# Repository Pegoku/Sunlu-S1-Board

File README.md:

# Sunlu S1 Filament Dryer Controller

Drop-in replacement controller board for the Sunlu S1 filament dryer. Features an STM32C011F4P6 microcontroller, 1.8" ST7735 TFT display, dual NTC temperature sensing, and precise PWM heater control; all optimized to fit in just 16 KB of flash. 

## Table of Contents
- [Overview](#overview)
- [Features](#features)
- [Quick Start](#quick-start)
- [User Guide](#user-guide)
- [Hardware](#hardware)
- [Technical Specs](#technical-specs)
- [Development](#development)
- [License](#license)

## Overview

Complete replacement for the stock Sunlu S1 control board, maintaining compatibility with the original heating element, chamber, and power connections. Adds a color TFT display in landscape mode and two-button navigation for precise temperature and time control (30–70°C configurable range, exceeding the stock 35–55°C limit).

The firmware uses integer-only math, dirty-check rendering, and batched SPI transfers to fit in the STM32C011's tiny 16 KB flash with room to spare.

### Gallery

Final build

<details>
<Summary>PCB</Summary>

</details>

## Features

### Display & Control
- **1.8" ST7735 TFT**: 160×128 px landscape, 16-bit RGB565 color
- **Two-button interface**: short-press (select/increment), long-press (toggle/cancel)
- **Three screens**: Main Status, Set Temperature, Set Time
- **Smart rendering**: dirty-check updates (only changed fields), instant button response

### Temperature & Heater Regulation
- **Dual NTC thermistors**: air temp (displayed) + heater element (safety)
- **Proportional PWM control** (~488 Hz): ramps heater power based on error from target
- **Dual safety cutoffs**: absolute (85°C) and dynamic (target + 5°C margin)
- **Integer-only lookup**: 11-point table with linear interpolation, no floating-point library
- **Fan control**: full speed during drying and overheat emergency

### Firmware Design
- **~600 lines**: single-loop, no RTOS/filesystem
- **~13 KB flash / ~2 KB RAM**: 80% flash usage, 33% RAM usage
- **Batched SPI**: 128-byte buffer (~100× faster than byte-by-byte)
- **Minimal font**: 5×7 bitmap, 29 glyphs only
- **No soft-float**: integer NTC lookup saves ~4 KB

## Quick Start

### Build
Requires `arm-none-eabi-gcc`, `cmake`, and `cube-cmake` installed.

```sh
cd Code
cmake --preset Debug
cmake --build build/Debug --target Code
```

### Flash
Using `st-flash`:

```sh
st-flash write build/Debug/Code.bin 0x08000000
```

Or use the VS Code task "Build and Flash" if configured.

## User Guide

### Main Screen (Status & Control)
- **Top**: Air temperature, Countdown timer (HH:MM)
- **Middle**: Current state (IDLE/RUN/PAUSE), target temperature setting
- **Bottom**: Action hints: BTN1=set, BTN2=start/pause/resume, hold BTN2=stop/reset

<details>
<summary>Example Main Screen</summary>

.jpg)

</details>

### Set Temperature Screen
- **Value**: Current target in °C
- **Controls**: 
  - **Short BTN1**: increment (or decrement if toggled)
  - **Long BTN1**: toggle UP/DOWN mode, hints show current direction
  - **Short BTN2**: confirm & advance to Set Time
  - **Long BTN2**: cancel & return to Main

<details>
<summary>Example Set Temp Screen</summary>

</details>

### Set Time Screen
- **Value**: Target drying time in HH:MM format
- **Controls**: Same as Set Temp (BTN1 for ±, long BTN1 to toggle, BTN2 to confirm/cancel)

<details>
<summary>Example Set Time Screen</summary>

.jpg)
</details>

### Operation
1. Press BTN1 on Main Screen → Set Temperature
2. Adjust with BTN1 (short = increment, long = toggle direction, watch hints)
3. Press BTN2 → Set Time
4. Adjust similarly, then press BTN2 → firmware returns to Main and **starts drying**
5. Monitor progress on Main Screen; press BTN2 to pause/resume
6. Hold BTN2 to stop and reset (returns to IDLE)

## Hardware

### Pinout & Connections
| Function | Pin | Module | Notes |
|----------|-----|--------|-------|
| Display CS | PB7 | SPI1 | ST7735 chip select |
| Display DC | PA3 | SPI1 | Data/Command |
| Display RES | PC14 | GPIO | Reset |
| Display BL | PA8 | GPIO | Backlight (always ON) |
| Display SPI | PA5, PA6, PA7 | SPI1 | CLK, MISO, MOSI |
| Button 1 | PA4 | GPIO | Up/Set (active LOW, pull-up) |
| Button 2 | PA5 | GPIO | Select/Confirm (active LOW, pull-up) |
| Heater PWM | PA0 | TIM1_CH1 | 16-bit PWM (0–65535 = 0–100%) |
| Fan PWM | PA1 | TIM17_CH1 | 16-bit PWM (0–65535 = 0–100%) |
| Air NTC | PA11 | ADC_CH11 | 100k thermistor, 3.3 V divider |
| Heater NTC | PA12 | ADC_CH12 | 100k thermistor, 3.3 V divider |
| LED | PA2 | GPIO | Status indicator (on during RUN/PAUSE) |

See [Code/Core/Inc/main.h](Code/Core/Inc/main.h) for full pin configuration.

## Technical Specs

### MCU & Peripherals
- **MCU**: STM32C011F4P6 (Cortex-M0+, 32 MHz, 16 KB flash, 6 KB RAM)
- **Display**: ST7735 1.8" TFT, 160×128 px, 16-bit RGB565, SPI @ 16 MHz
- **PWM**: TIM1 (heater) + TIM17 (fan), ~488 Hz, 16-bit resolution
- **ADC**: 12-bit, dual-channel NTC reading @ 500 ms

### Temperature & Timing
- **Range**: 30–70°C (configurable `TMIN`/`TMAX`)
- **NTC**: 100 K, B=3950, ~1°C resolution
- **Button poll**: 20 ms (30 ms debounce, 1 s long-press)
- **Display refresh**: 250 ms idle on Main screen, instant on changes
- **Countdown**: 1 s ticks

### Power
- **Input**: 24 V DC
- **Heater**: ≤48 W (PWM-controlled)
- **Fan**: ≤2 W (PWM-controlled)
- **MCU + Display**: ≤100 mA @ 3.3 V
## Development

### Structure
```
├── CMakeLists.txt              # Build config
├── Core/
│   ├── Inc/
│   │   ├── main.h              # Pin definitions, HAL config
│   │   ├── dryer.h             # Public firmware API
│   │   └── ...
│   └── Src/
│       ├── main.c              # Entry point, HAL init
│       ├── dryer.c             # Firmware (600 lines): display driver, UI, control
│       └── ...
├── Drivers/
│   ├── CMSIS/
│   ├── STM32C0xx_HAL_Driver/   # ST HAL
│   └── ...
└── cmake/                       # Toolchain files
```

### Modifying the Firmware
- Temperature limits: edit `TMIN`, `TMAX`, `TDEF` in [Code/Core/Src/dryer.c](Code/Core/Src/dryer.c)
- Time limits: edit `MMIN`, `MMAX`, `MDEF`
- Safety margin: change `stmp + 5` in `Regulate()` function
- NTC calibration: update `ntc[]` lookup table in [Code/Core/Src/dryer.c](Code/Core/Src/dryer.c)

## Bill of Materials

See [BOM.csv](BOM.csv) for the complete component list and part numbers.

## License

This work is licensed under a
[Creative Commons Attribution-NonCommercial 4.0 International License][cc-by-nc].

[![CC BY-NC 4.0][cc-by-nc-image]][cc-by-nc]

[cc-by-nc]: https://creativecommons.org/licenses/by-nc/4.0/
[cc-by-nc-image]: https://licensebuttons.net/l/by-nc/4.0/88x31.png
[cc-by-nc-shield]: https://img.shields.io/badge/License-CC%20BY--NC%204.0-lightgrey.svg

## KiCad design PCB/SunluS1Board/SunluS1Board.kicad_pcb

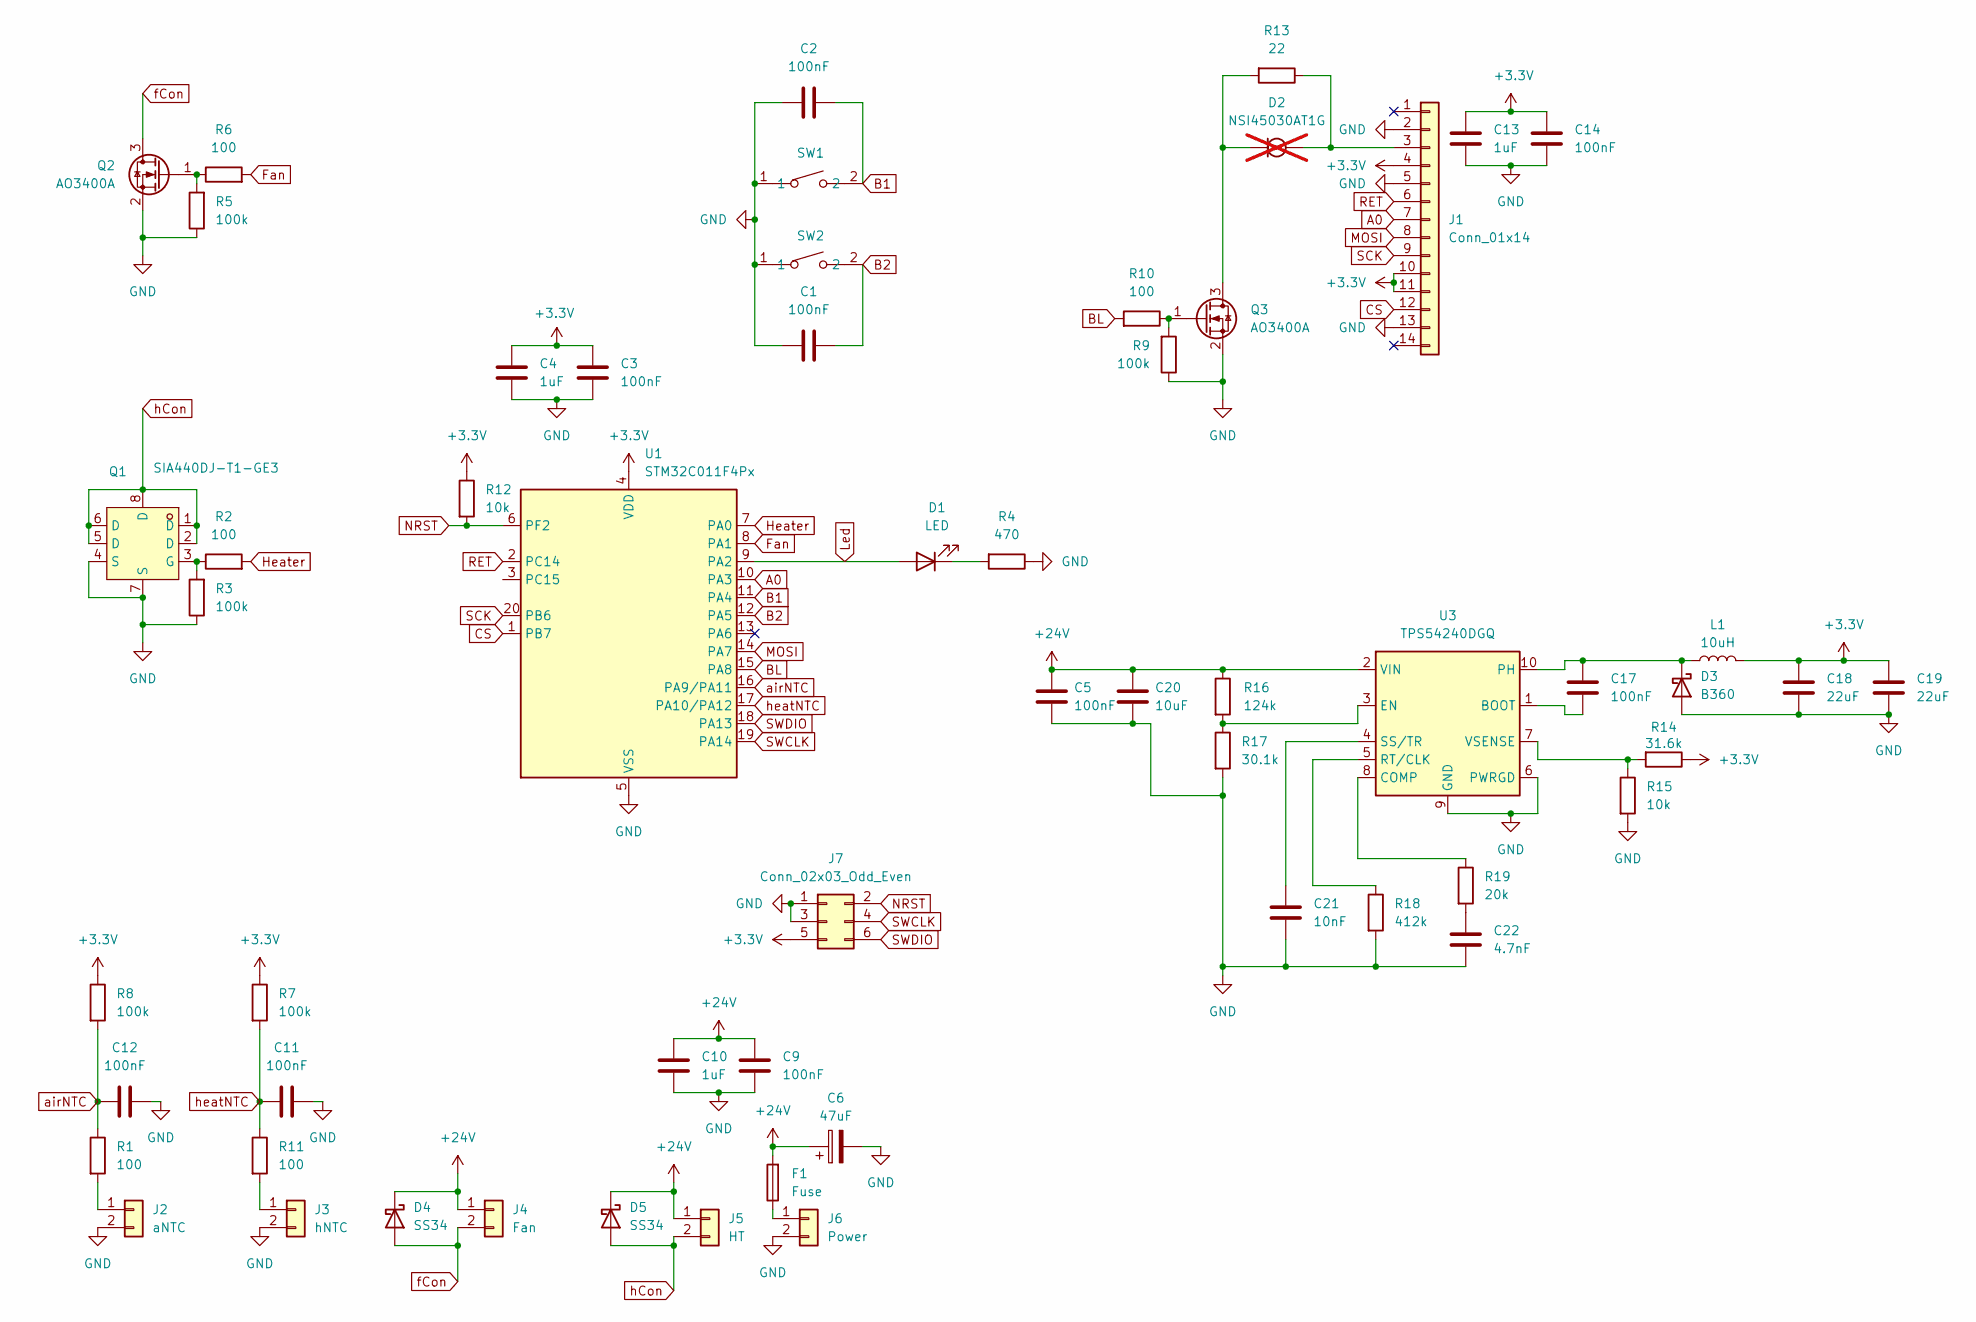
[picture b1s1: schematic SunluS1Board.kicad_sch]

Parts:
C1, C2, C3, C5, C9, C11, C12, C14, C17: 100nF; C_0603_1608Metric
C4, C10, C13: 1uF; C_0805_2012Metric
C6: 47uF; CAP-SMD_BD6.3-L6.6-W6.6-FD
C18, C19: 22uF; C_0805_2012Metric
C20: 10uF; C_1210_3225Metric
C21: 10nF; C_0603_1608Metric
C22: 4.7nF; C_0603_1608Metric
D1: LED; LED_0603_1608Metric
D2: NSI45030AT1G; D_SOD-123; not fitted
D3: B360; D_SMB
D4, D5: SS34; D_SMA
F1: Fuse; Fuse_1206_3216Metric
J1: Conn_01x14; STP0177A-128160
J2: aNTC; Molex_PicoBlade_53048-0210_1x02_P1.25mm_Horizontal
J3: hNTC; Molex_PicoBlade_53048-0210_1x02_P1.25mm_Horizontal
J4: Fan; CONN-TH_2P-P2.54_AXH-2AW-11
J5: HT; CONN-TH_2P-P2.54_AXH-2AW-11
J6: Power; CONN-TH_2P-P2.54_AXH-2AW-11
J7: Conn_02x03_Odd_Even; PinHeader_2x03_P2.54mm_Vertical_SMD
L1: 10uH; L_APV_ANR4020
Q1: SIA440DJ-T1-GE3; SC-70-6L_L2.0-W2.0-P0.65-BL; LCSC Part C727349
Q2, Q3: AO3400A; SOT-23
R1, R2, R6, R10, R11: 100; R_0603_1608Metric
R3, R5, R7, R8, R9: 100k; R_0603_1608Metric
R4: 470; R_0603_1608Metric
R12, R15: 10k; R_0603_1608Metric
R13: 22; R_0603_1608Metric
R14: 31.6k; R_0603_1608Metric
R16: 124k; R_0603_1608Metric
R17: 30.1k; R_0603_1608Metric
R18: 412k; R_0603_1608Metric
R19: 20k; R_0603_1608Metric
SW1, SW2: CS1213AGF260; SW-SMD_L3.9-W3.0-P4.45
U1: STM32C011F4Px; TSSOP-20_4.4x6.5mm_P0.65mm
U3: TPS54240DGQ; HVSSOP-10-1EP_3x3mm_P0.5mm_EP1.83x1.89mm_ThermalVias

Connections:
+3.3V: C3.1, C4.1, C13.1, C14.1, C18.1, C19.1, J1.4, J1.10, J1.11, J7.5, L1.2, R7.1, R8.1, R12.1, R14.1, U1.4 (VDD)
+24V: C5.1, C6.1, C9.1, C10.1, C20.1, D4.1 (K), D5.1 (K), F1.2, J4.1, J5.1, R16.1, U3.2 (VIN)
A0: J1.7, U1.10 (PA3)
B1: C2.1, SW1.2, U1.11 (PA4)
B2: C1.1, SW2.2, U1.12 (PA5)
BL: R10.2, U1.15 (PA8)
CS: J1.12, U1.1 (PB7)
Fan: R6.2, U1.8 (PA1)
GND: C1.2, C2.2, C3.2, C4.2, C5.2, C6.2, C9.2, C10.2, C11.2, C12.2, C13.2, C14.2, C18.2, C19.2, C20.2, C21.2, C22.2, D3.2 (A), J1.2, J1.5, J1.13, J2.2, J3.2, J6.2, J7.1, J7.3, Q1.4 (S), Q1.7 (S), Q2.2 (S), Q3.2 (S), R3.1, R4.1, R5.1, R9.1, R15.2, R17.2, R18.2, SW1.1, SW2.1, U1.5 (VSS), U3.6 (PWRGD), U3.9 (GND), U3.11 (GND)
Heater: R2.2, U1.7 (PA0)
Led: D1.2 (A), U1.9 (PA2)
MOSI: J1.8, U1.14 (PA7)
NRST: J7.2, R12.2, U1.6 (PF2)
unnamed: C22.1, R19.2
unnamed: D1.1 (K), R4.2
unnamed: D2.2 (A), J1.3, R13.1
unnamed: D2.1 (K), Q3.3 (D), R13.2
unnamed: C17.1, D3.1 (K), L1.1, U3.10 (PH)
unnamed: J2.1, R1.2
unnamed: J3.1, R11.2
unnamed: F1.1, J6.1
unnamed: Q1.3 (G), R2.1, R3.2
unnamed: Q2.1 (G), R5.2, R6.1
unnamed: Q3.1 (G), R9.2, R10.1
unnamed: C17.2, U3.1 (BOOT)
unnamed: R19.1, U3.8 (COMP)
unnamed: R16.2, R17.1, U3.3 (EN)
unnamed: R18.1, U3.5 (RT/CLK)
unnamed: C21.1, U3.4 (SS/TR)
unnamed: R14.2, R15.1, U3.7 (VSENSE)
RET: J1.6, U1.2 (PC14)
SCK: J1.9, U1.20 (PB6)
SWCLK: J7.4, U1.19 (PA14)
SWDIO: J7.6, U1.18 (PA13)
airNTC: C12.1, R1.1, R8.2, U1.16 (PA9/PA11)
fCon: D4.2 (A), J4.2, Q2.3 (D)
hCon: D5.2 (A), J5.2, Q1.1 (D), Q1.2 (D), Q1.5 (D), Q1.6 (D), Q1.8 (D)
heatNTC: C11.1, R7.2, R11.1, U1.17 (PA10/PA12)

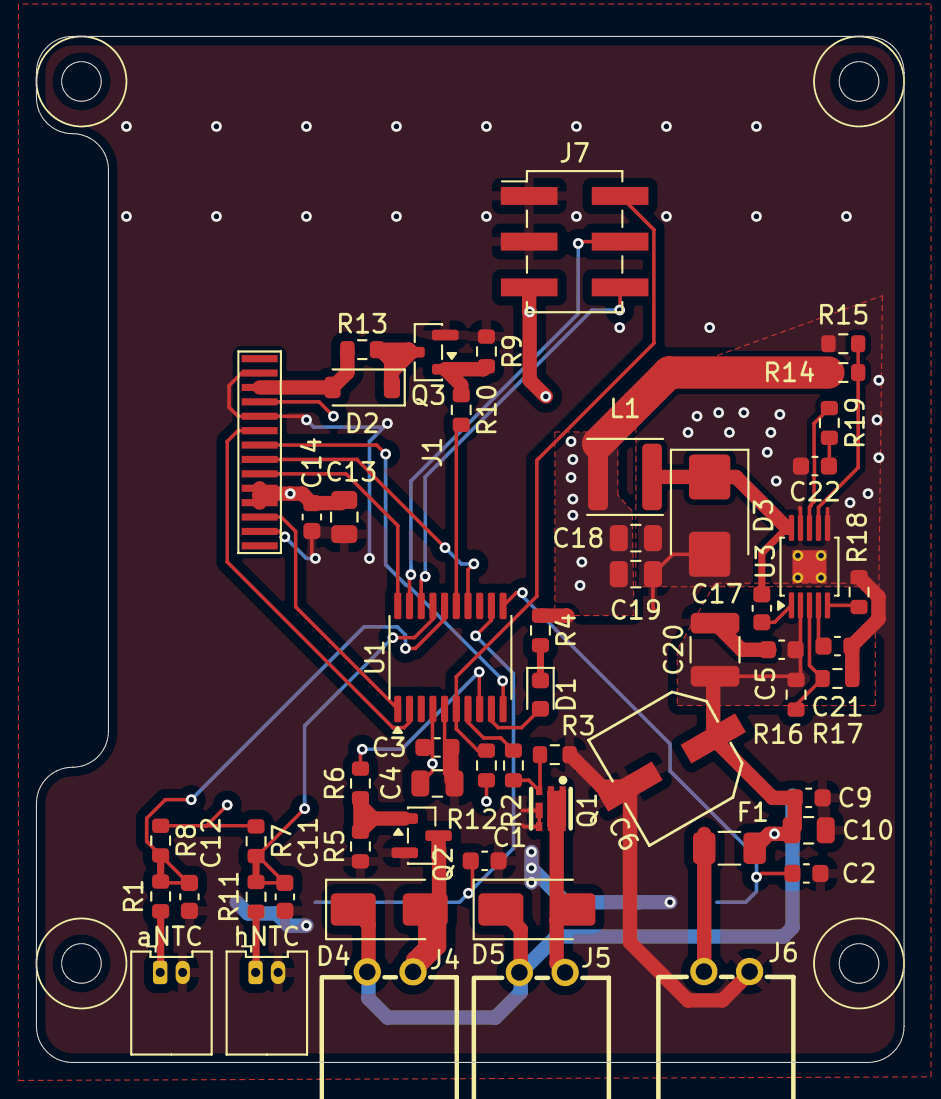
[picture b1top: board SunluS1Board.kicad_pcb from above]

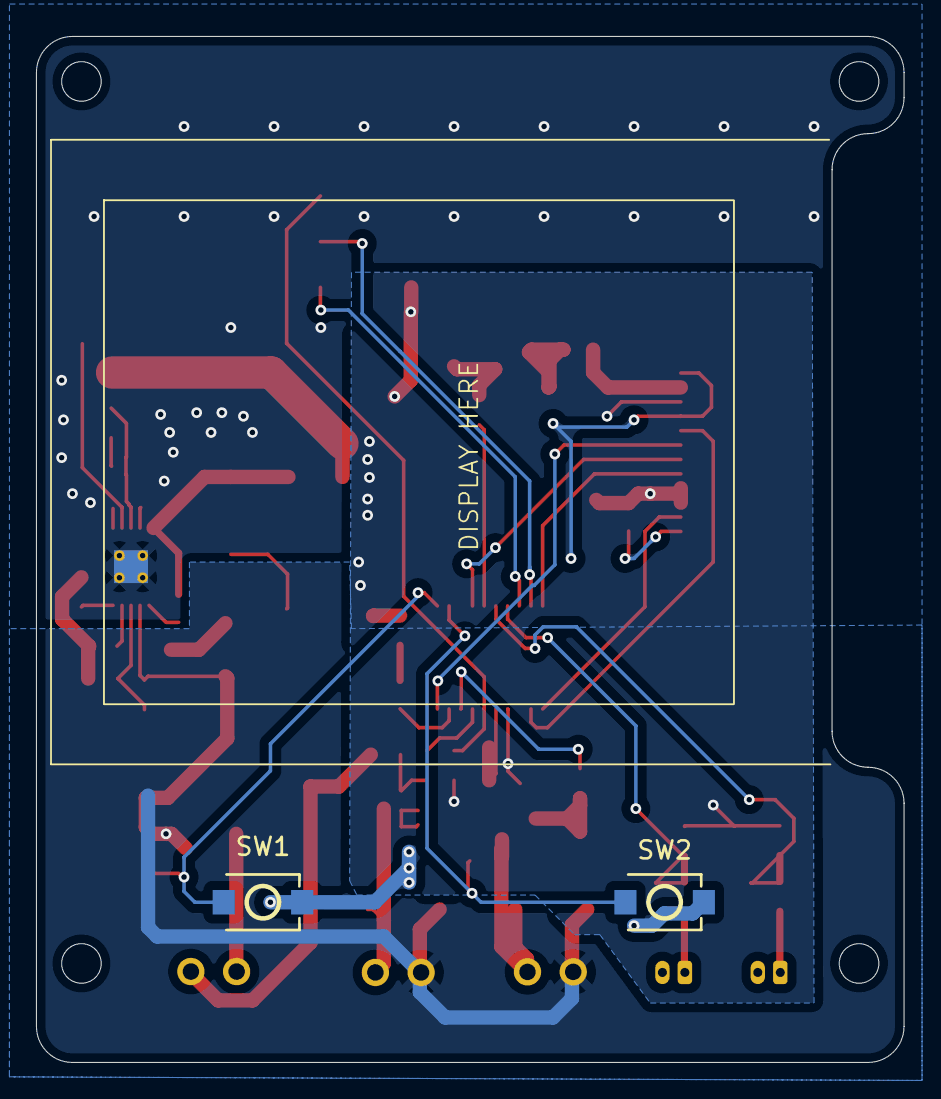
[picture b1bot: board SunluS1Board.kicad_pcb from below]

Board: 2 copper layers, 48.2 x 57.0 mm, 58 parts (2 on the bottom side), 38 nets.

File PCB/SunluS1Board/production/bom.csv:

Designator,Footprint,Quantity,Value,LCSC Part #
"C1, C11, C12, C14, C17, C2, C3, C5, C9",0603,9,100nF,
"C10, C13, C4",0805,3,1uF,
"C18, C19",0805,2,22uF,
C20,1210,1,10uF,
C21,0603,1,10nF,
C22,0603,1,4.7nF,
C6,CAP-SMD_BD6.3-L6.6-W6.6-FD,1,47uF,
D1,0603,1,LED,
D2,D_SOD-123,1,NSI45030AT1G,
D3,D_SMB,1,B360,
"D4, D5",D_SMA,2,SS34,
F1,1206,1,Fuse,
J1,STP0177A-128160,1,Conn_01x14,
J2,Molex_PicoBlade_53048-0210_1x02_P1.25mm_Horizontal,1,aNTC,
J3,Molex_PicoBlade_53048-0210_1x02_P1.25mm_Horizontal,1,hNTC,
J4,CONN-TH_2P-P2.54_AXH-2AW-11,1,Fan,
J5,CONN-TH_2P-P2.54_AXH-2AW-11,1,HT,
J6,CONN-TH_2P-P2.54_AXH-2AW-11,1,Power,
J7,PinHeader_2x03_P2.54mm_Vertical_SMD,1,Conn_02x03_Odd_Even,
L1,L_APV_ANR4020,1,10uH,
Q1,SC-70-6L_L2.0-W2.0-P0.65-BL,1,SIA440DJ-T1-GE3,C727349
"Q2, Q3",SOT-23,2,AO3400A,
"R1, R10, R11, R2, R6",0603,5,100,
"R12, R15",0603,2,10k,
R13,0603,1,22,
R14,0603,1,31.6k,
R16,0603,1,124k,
R17,0603,1,30.1k,
R18,0603,1,412k,
R19,0603,1,20k,
"R3, R5, R7, R8, R9",0603,5,100k,
R4,0603,1,470,
"SW1, SW2",SW-SMD_L3.9-W3.0-P4.45,2,CS1213AGF260,
U1,TSSOP-20_4.4x6.5mm_P0.65mm,1,STM32C011F4Px,
U3,HVSSOP-10-1EP_3x3mm_P0.5mm_EP1.83x1.89mm_ThermalVias,1,TPS54240DGQ,

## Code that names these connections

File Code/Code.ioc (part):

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Mcu.Name=STM32C011F(4-6)Px
Mcu.Package=TSSOP20
Mcu.UserName=STM32C011F4Px
PA0.GPIOParameters=GPIO_Label
PA0.GPIO_Label=heater
PA0.Signal=S_TIM1_CH1
PA1.GPIOParameters=GPIO_Label
PA1.GPIO_Label=fan
PA1.Signal=S_TIM17_CH1
PA11\ [PA9].GPIOParameters=GPIO_Label
PA11\ [PA9].GPIO_Label=airNTC
PA11\ [PA9].Mode=IN11
PA11\ [PA9].Signal=ADC1_IN11
PA12\ [PA10].GPIOParameters=GPIO_Label
PA12\ [PA10].GPIO_Label=heatNTC
PA12\ [PA10].Mode=IN12
PA12\ [PA10].Signal=ADC1_IN12
PA13.Mode=Serial_Wire
PA13.Signal=DEBUG_SWDIO
PA14-BOOT0.Mode=Serial_Wire
PA14-BOOT0.Signal=DEBUG_SWCLK
PA2.GPIOParameters=GPIO_Label
PA2.GPIO_Label=led
PA2.Signal=GPIO_Output
PA3.GPIOParameters=GPIO_Label
PA3.GPIO_Label=A0
PA3.Signal=GPIO_Output
PA4.GPIOParameters=GPIO_Label
PA4.GPIO_Label=b1
PA4.Signal=GPIO_Input
PA5.GPIOParameters=GPIO_Label
PA5.GPIO_Label=b2
PA5.Signal=GPIO_Input
PA7.Mode=Simplex_Bidirectional_Master
PA7.Signal=SPI1_MOSI
PA8.GPIOParameters=GPIO_Label
PA8.GPIO_Label=BL
PA8.Signal=GPIO_Output
PB6.Mode=Simplex_Bidirectional_Master
PB6.Signal=SPI1_SCK
PB7.GPIOParameters=GPIO_Label
PB7.GPIO_Label=CS
PB7.Signal=GPIO_Output
PC14-OSCX_IN\ (PC14).GPIOParameters=GPIO_Label
PC14-OSCX_IN\ (PC14).GPIO_Label=RES
PC14-OSCX_IN\ (PC14).Signal=GPIO_Output
RCC.HSE_VALUE=8000000
RCC.SYSCLKFreq_VALUE=12000000
board=custom

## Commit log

2025-12-07 LICENSE
2025-12-08 Create MX project
2025-12-08 use SPI instead of I2C
2025-12-08 start base schematic
2025-12-09 display
2025-12-13 edit
2025-12-15 finish schematic
2025-12-15 add swd header
2025-12-15 refine schematic
2025-12-15 use half duplex for the spi
2025-12-15 more decaps
2025-12-15 custom footprint
2025-12-15 add current regulator to display
2025-12-15 add resistor fallback
2025-12-15 fix footprint
2025-12-17 finish schematic fr
2025-12-17 start pcb
2025-12-17 continue PCB
2025-12-17 update footprint
2025-12-17 most placement done
2025-12-17 placement done
2025-12-17 mostly routed
2025-12-18 continue routing
2025-12-18 fillet pcb
2025-12-18 DRC and 3d models
2025-12-18 fixes
2025-12-18 fixes2
2025-12-18 fix buttons
2025-12-18 schematic
2025-12-21 fix schematic
2025-12-21 start buck design
2025-12-21 schematic: finish buck
2025-12-21 continue buck
2025-12-22 footprints
2025-12-22 start buck pcb
2025-12-22 f*** I placed and routed the buck at the wrong layer...
2025-12-22 mostly finsish pcb, again
2025-12-22 finish V2
2025-12-22 finish pcb and BOM
2025-12-22 finish BOM
2025-12-22 add display
2026-02-05 stm32 stuff + blink!
2026-02-05 uploads!
2026-02-06 bl toggles
2026-02-06 display stripes
2026-02-06 fix digits
2026-02-06 build in release mode + ntc
2026-02-06 fix dot rendering
2026-02-07 fix display
2026-02-07 base works!
2026-02-07 use int
2026-02-07 v0.1
2026-02-07 v0.2 - horizontal UI
2026-02-07 optimize redraw logic
2026-02-07 add direction control for temperature and time adjustments
2026-02-08 screenBuffer for faster refresh
2026-02-08 use htemp to regulate heater temperature
2026-02-08 README
2026-02-08 readme images
2026-02-08 readme links
2026-02-08 typo
2026-02-08 add images
2026-02-08 Fixes for V2
